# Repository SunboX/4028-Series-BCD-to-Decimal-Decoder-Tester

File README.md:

# 4028-Series-BCD-to-Decimal-Decoder-Tester

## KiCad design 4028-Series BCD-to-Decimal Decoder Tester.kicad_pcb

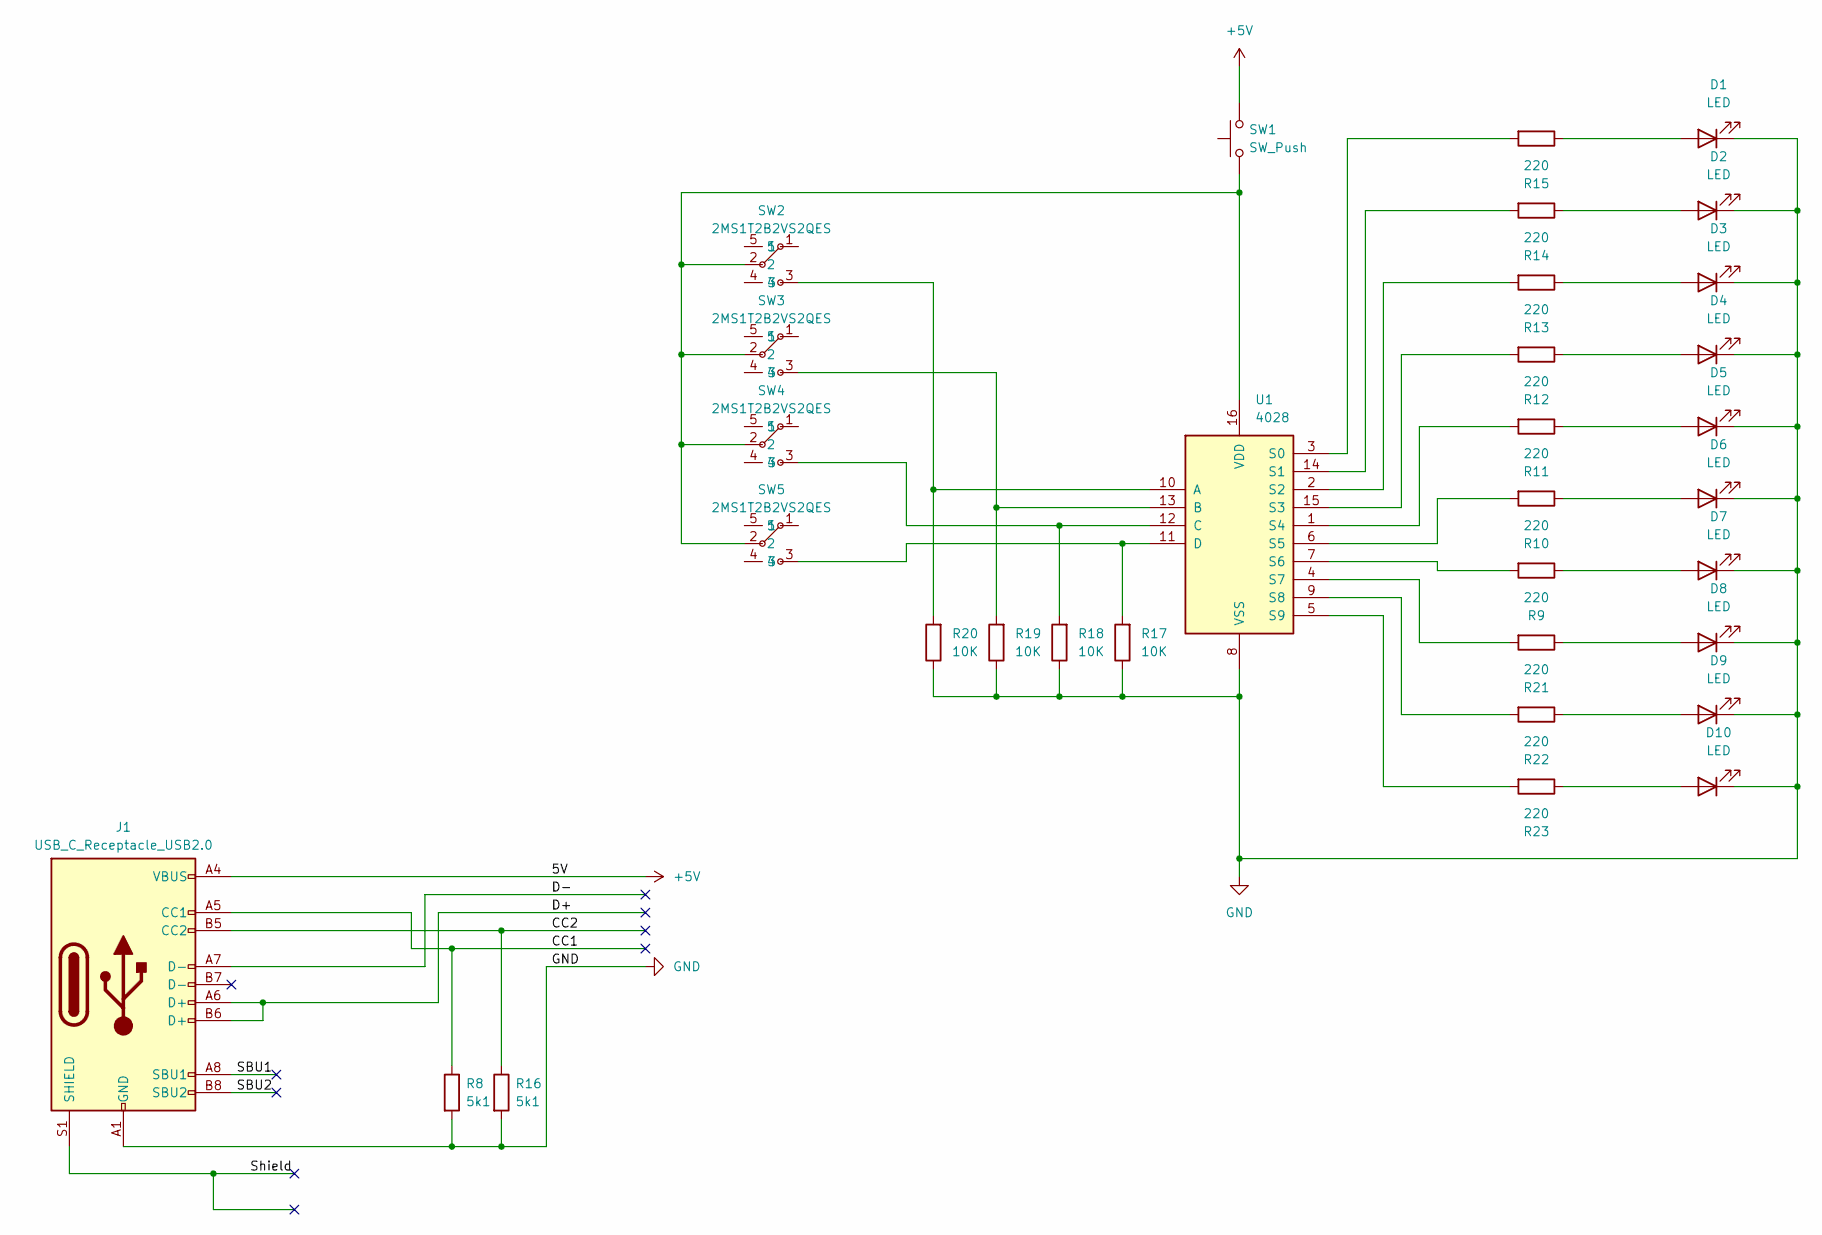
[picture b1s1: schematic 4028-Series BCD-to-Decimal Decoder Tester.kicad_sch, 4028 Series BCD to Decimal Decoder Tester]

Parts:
D1, D2, D3, D4, D5, D6, D7, D8, D9, D10: LED; LED_0805_2012Metric_Pad1.15x1.40mm_HandSolder
J1: USB_C_Receptacle_USB2.0; USB_C_Receptacle_GCT_USB4105-xx-A_16P_TopMnt_Horizontal; LCSC C2982555
R8, R16: 5k1; R_0805_2012Metric_Pad1.20x1.40mm_HandSolder; LCSC C23186
R9, R10, R11, R12, R13, R14, R15, R21, R22, R23: 220; R_0805_2012Metric_Pad1.20x1.40mm_HandSolder
R17, R18, R19, R20: 10K; R_0805_2012Metric_Pad1.20x1.40mm_HandSolder
SW1: SW_Push; SW_B3F-1000
SW2, SW3, SW4, SW5: 2MS1T2B2VS2QES; SW-TH_2MS1T2B2VS2QES; LCSC Part C545202
U1: 4028; DIP_Socket-16_W4.3_W5.08_W7.62_W10.16_W10.9_3M_216-3340-00-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

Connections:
+5V: J1.A4 (VBUS), J1.A9 (VBUS), J1.B4 (VBUS), J1.B9 (VBUS), SW1.3
/CC1: J1.A5 (CC1), R8.1
/CC2: J1.B5 (CC2), R16.1
/D+: J1.A6 (D+), J1.B6 (D+)
/D-: J1.A7 (D-)
/SBU1: J1.A8 (SBU1)
/SBU2: J1.B8 (SBU2)
/Shield: J1.S1 (SHIELD)
/Shield_1: J1.S1 (SHIELD)
/Shield_2: J1.S1 (SHIELD)
/Shield_3: J1.S1 (SHIELD)
GND: D1.1 (K), D2.1 (K), D3.1 (K), D4.1 (K), D5.1 (K), D6.1 (K), D7.1 (K), D8.1 (K), D9.1 (K), D10.1 (K), J1.A1 (GND), J1.A12 (GND), J1.B1 (GND), J1.B12 (GND), R8.2, R16.2, R17.1, R18.1, R19.1, R20.1, U1.8 (VSS)
unnamed: D1.2 (A), R15.1
unnamed: D2.2 (A), R14.1
unnamed: D3.2 (A), R13.1
unnamed: D4.2 (A), R12.1
unnamed: D5.2 (A), R11.1
unnamed: D6.2 (A), R10.1
unnamed: D7.2 (A), R9.1
unnamed: D8.2 (A), R21.1
unnamed: D9.2 (A), R22.1
unnamed: D10.2 (A), R23.1
unnamed: R20.2, SW2.3, U1.10 (A)
unnamed: R19.2, SW3.3, U1.13 (B)
unnamed: R18.2, SW4.3, U1.12 (C)
unnamed: R17.2, SW5.3, U1.11 (D)
unnamed: R15.2, U1.3 (S0)
unnamed: R14.2, U1.14 (S1)
unnamed: R13.2, U1.2 (S2)
unnamed: R12.2, U1.15 (S3)
unnamed: R11.2, U1.1 (S4)
unnamed: R10.2, U1.6 (S5)
unnamed: R9.2, U1.7 (S6)
unnamed: R21.2, U1.4 (S7)
unnamed: R22.2, U1.9 (S8)
unnamed: R23.2, U1.5 (S9)
unnamed: SW1.1, SW2.2, SW3.2, SW4.2, SW5.2, U1.16 (VDD)

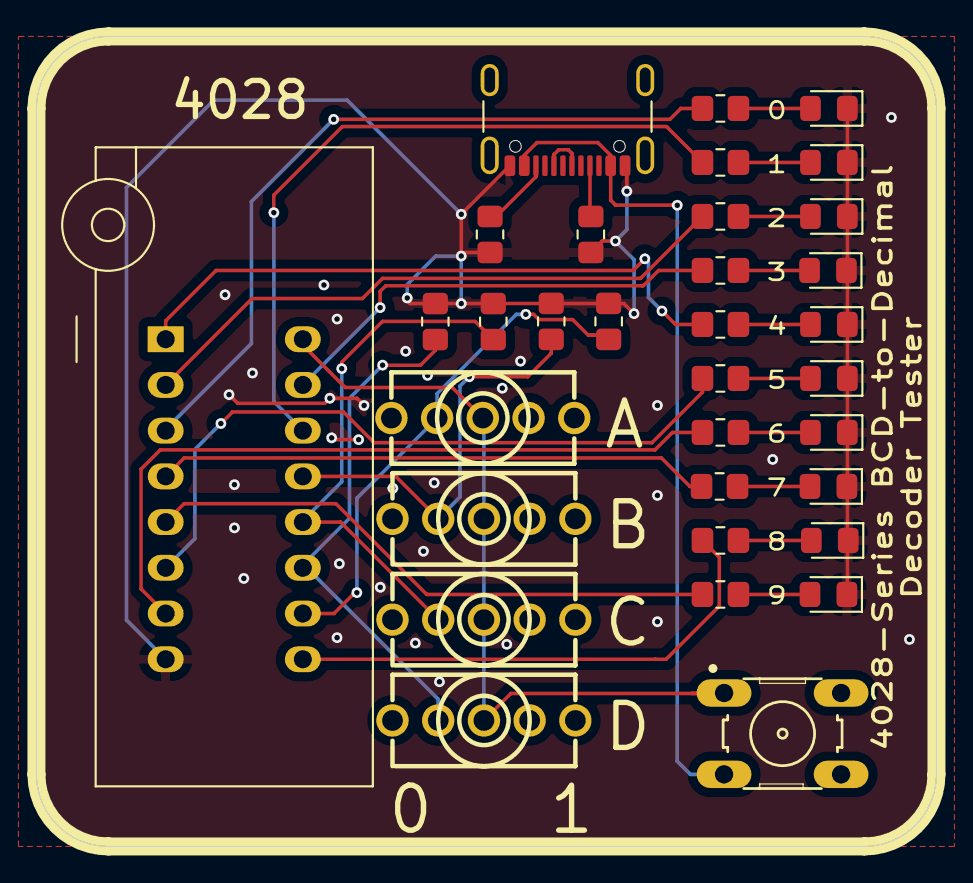
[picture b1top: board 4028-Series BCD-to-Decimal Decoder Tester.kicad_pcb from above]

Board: 2 copper layers, 50.0 x 45.0 mm, 33 parts (0 on the bottom side), 30 nets.

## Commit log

2025-07-15 ༼ つ ◕_◕ ༽つ initial commit
2025-07-20 Fixed LED ordering
